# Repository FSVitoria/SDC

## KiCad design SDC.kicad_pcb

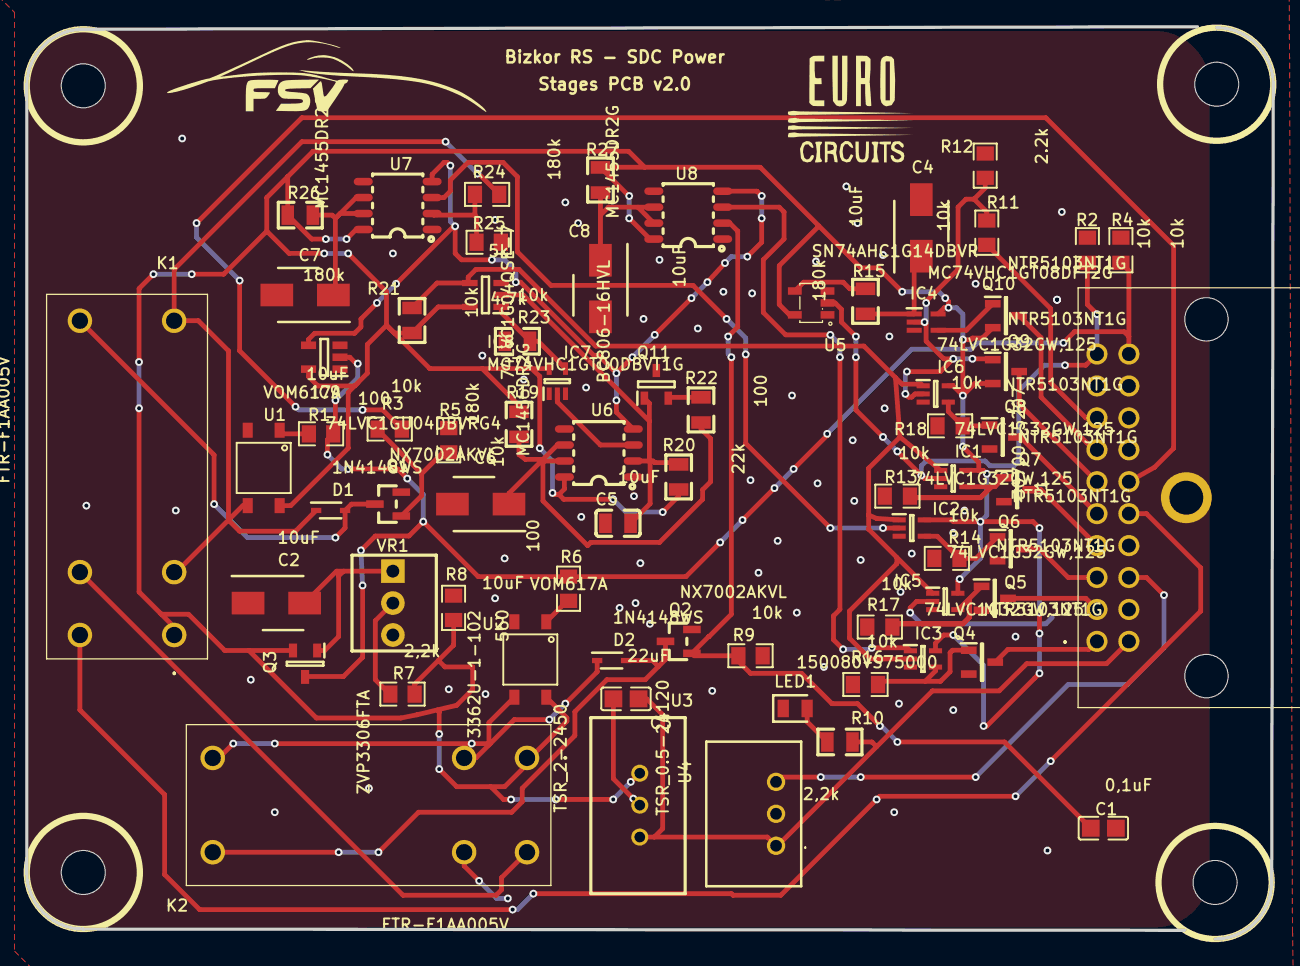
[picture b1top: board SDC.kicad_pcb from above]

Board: 2 copper layers, 99.2 x 72.6 mm, 74 parts (0 on the bottom side), 51 nets.

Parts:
C1: 0,1uF; C0805
C2, C4, C6, C7, C8: 10uF; CAPAE430X610N
C3: 22uF; C0805
C5: 10uF; C0805
D1, D2: 1N4148WS; SODFL2512X90N
Hole_gge38057: Hole_gge38057
Hole_gge38063: Hole_gge38063
Hole_gge38066: Hole_gge38066
Hole_gge44267: Hole_gge44267
IC1, IC2, IC3, IC5, IC6: 74LVC1G32GW,125; SOT65P212X110-5N
IC4: MC74VHC1GT08DFT2G; SOT65P210X110-5N
IC7: 74LVC1G04QSE-7; SOT65P210X100-5N
IC8: MC74VHC1GT00DBVT1G; SOT95P275X110-5N
IC9: 74LVC1GU04DBVRG4; SOT95P280X145-5N
J1: 30700-5207; 307005207
K1, K2: FTR-F1AA005V; FTRF1AA005V
LED1: 150080VS75000; LEDC2012X80N
Q1, Q2: NX7002AKVL; TO-236AB_L2.9-W1.3-P0.95-LS2.3-BR
Q3: ZVP3306FTA; SOT96P240X100-3N
Q4, Q5, Q6, Q7, Q8, Q9, Q10: NTR5103NT1G; SOT95P237X101-3N
Q11: BC806-16HVL; SOT95P230X110-3N
R1, R6: 100; R0805_NEW
R2, R4, R13, R14, R16, R17, R18, R21, R23: 10k; R0805
R3, R5, R9, R11: 10k; R0805_NEW
R7: 2,2k; R0805_NEW
R8: 560; R0805_NEW
R10: 2,2k; R0805
R12: 2.2k; R0805_NEW
R15, R19, R26, R27: 180k; R0805
R20: 22k; R0805
R22: 100; R0805
R24: 5k; R0805_NEW
R25: 4.7k; R0805_NEW
U1, U2: VOM617A; SOP-4
U3: TSR_2-2450; TSR-2
U4: TSR_0.5-24120; TSR0524120
U5: SN74AHC1G14DBVR; SOT-23-5_L3.0-W1.7-P0.95-LS2.8-BR
U6, U7, U8: MC1455DR2G; SOIC-8_L4.9-W3.9-P1.27-LS6.0-BL
VR1: 3362U-1-102; 3362U-2

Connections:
+5V: IC1.5, IC2.5, IC3.5, IC4.5, IC5.5, IC6.5, IC7.5, IC8.5, IC9.5, J1.14, K1.1, K2.1, Q3.2, Q9.2, Q10.2, R7.2, R8.2, R19.2, R20.2, R21.2, R26.2, R27.2, U1.4, U2.4, U3.3, U5.5, U6.8, U7.8, U8.8
+12V: J1.13, U4.3
+24V: C3.2, J1.11, R10.1, U3.1, U4.1
AMSFAULTLEDDRIVER: IC3.4, Q4.1, R16.2
AMS_FAULT_TIMED: IC3.1, U8.3
AMS_LED: J1.1, Q4.3
AMS_ST: C1.1, J1.19, Q2.1, R9.1, U8.2
BSPDLEDDRIVER: IC5.4, Q5.1, R17.2
BSPD_LED: J1.2, Q5.3
BSPD_ST: IC5.2, J1.17
GND: C1.2, C2.1, C3.1, C4.2, C5.1, C6.2, C7.2, C8.2, IC1.3, IC2.3, IC3.3, IC4.3, IC5.3, IC6.3, IC7.3, IC8.3, IC9.3, J1.12, LED1.1, Q1.2, Q2.2, Q4.2, Q5.2, Q6.2, Q7.2, Q8.2, Q11.3, R2.1, R4.1, R5.1, R8.1, R9.2, R12.1, R13.1, R14.1, R16.1, R17.1, R18.1, R23.1, R25.1, U1.2, U2.2, U3.2, U4.2, U5.3, U6.1, U7.1, U8.1
IC4_1: C4.1, IC4.1, R15.1
IC7_4: IC7.4, IC8.1, R23.2
IMDFAULTLEDDRIVER: IC2.4, Q6.1, R14.2
IMD_FAULT_5V: D1.1, K1.2, K1.4, R24.1, U1.3
IMD_FAULT_TIMED: IC2.2, U7.3
IMD_LED: J1.3, Q6.3
IMD_ST: J1.16, R3.2
K1_5: D1.2, K1.5, Q1.3
K1_7: K1.7, K2.8
K2_2: D2.1, K2.2, K2.4, U2.3
K2_5: D2.2, K2.5, Q2.3
Q10_1: IC4.4, Q10.1
R1_1: R1.1, U1.1
R2D_BUT_EN: J1.7, Q10.3
R3_1: Q1.1, R3.1, R5.2
R6_1: R6.1, U2.1
R7_1: R7.1, VR1.2
R10_2: LED1.2, R10.2
R22_1: Q11.2, R22.1
R27_1: C8.1, R27.1, U8.6, U8.7
RESET: IC9.4, U6.4, U7.4, U8.4
RES_B_2: IC9.2, J1.10, Q3.3, R1.2, R2.2, R6.2
SDC+: J1.8, R11.1
SDC+LEDDRIVER: IC6.4, Q8.1, R18.2
SDC+_5V: IC4.2, IC6.2, Q9.1, R11.2, R12.2
SDC+_LED: J1.5, Q8.3
SDC_IN: J1.15, K1.8
SDC_OUT: J1.18, K2.7
TSOFFLEDDRIVER: IC1.4, Q7.1, R13.2
TS_BUT_EN: J1.6, Q9.3
TS_OFF_LED: J1.4, Q7.3
TS_STATE: IC1.2, J1.20, R4.2, U5.2
U5_4: R15.2, U5.4
U6_2: C5.2, IC8.2, Q11.1, R20.1, U6.2
U6_3: IC7.2, U6.3
U6_6: C6.1, R19.1, R22.2, U6.6, U6.7
U7_2: R24.2, R25.2, U7.2
U7_6: C7.1, R26.1, U7.6, U7.7
VISIBLECHECK: IC1.1, IC2.1, IC3.2, IC5.1, IC6.1, IC8.4, R21.1
VR1_1: C2.2, Q3.1, VR1.1
